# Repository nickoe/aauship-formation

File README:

AAUSHIP
=======

This repo is devoted develop and test formation control on AAUSHIP

http://auv.aau.dk

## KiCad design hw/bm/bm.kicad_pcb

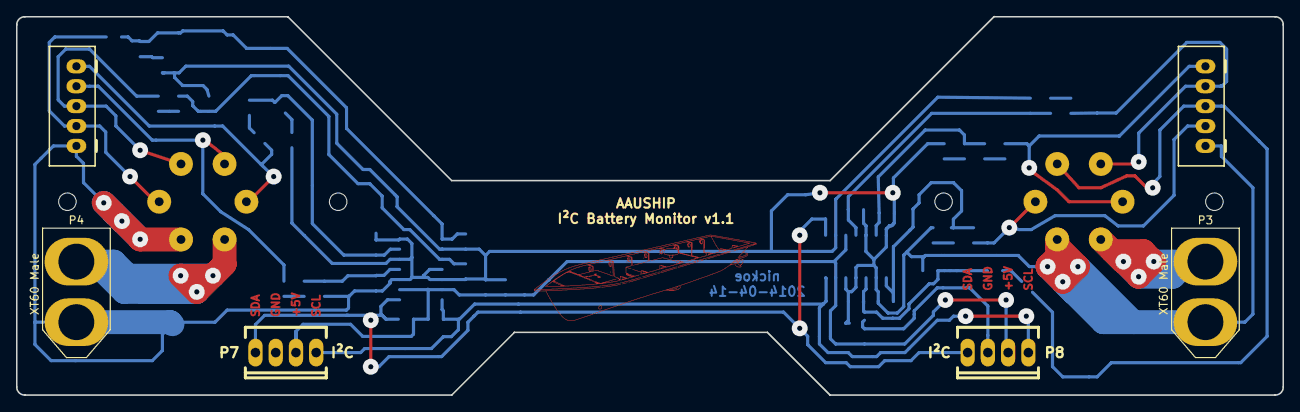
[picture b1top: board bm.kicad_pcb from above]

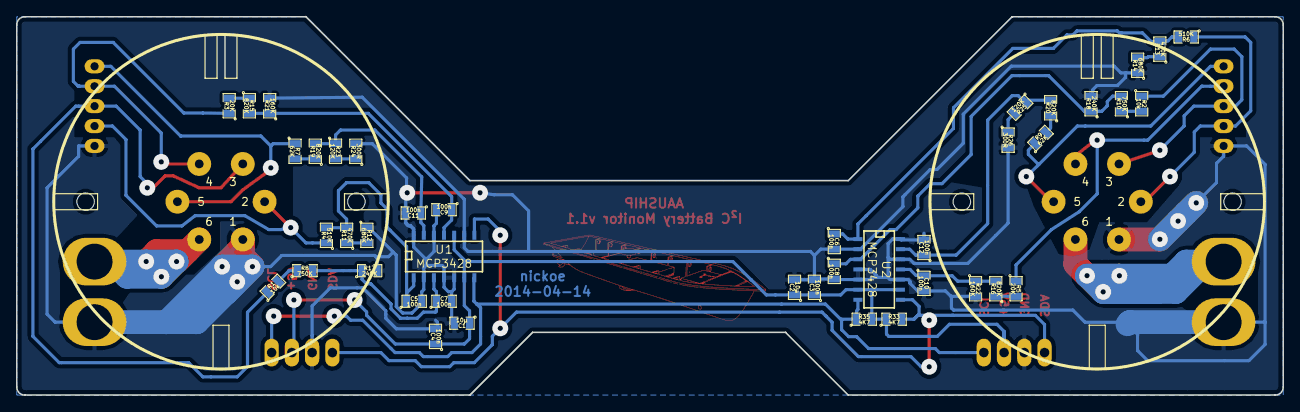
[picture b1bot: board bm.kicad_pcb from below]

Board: 2 copper layers, 159.0 x 47.5 mm, 51 parts (44 on the bottom side), 32 nets.

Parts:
C1, C2: 10µ; SM0805
C3, C4, C5, C6, C7, C8, C9, C10, C11, C12: 100n; SM0805
P1, P2: PX0707/06S; PX0707-S-6
P3, P4: XT60 Male; XT60
P5, P6: JST-XH; JST-B5B-XH-A
P7, P8: I²C; Socket_MOLEX-KK-RM2-54mm_Lock_4pin_straight
R1, R2: 10k; SM0805
R3, R5: 20K; SM0805
R4, R6: 510K; SM0805
R7, R9: 62K; SM0805
R8, R10: 750K; SM0805
R11, R13: 470K; SM0805
R12, R14: 680K; SM0805
R15, R16, R19, R20: 820K; SM0805
R17, R18: 240K; SM0805
R21, R22: 160K; SM0805
R23, R25: 120K; SM0805
R24, R26: 300R; SM0805
R33, R35: 4K7; SM0805
U1, U2: MCP3428; SO14E
VAL: aauship

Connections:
+5V: C1.1, C2.1, C3.1, C4.1, P7.2, P8.2, R33.1, R35.2, U1.6, U1.10, U2.6, U2.9
GND: C1.2, C2.2, C3.2, C4.2, C5.2, C6.2, C7.2, C8.2, C9.2, C10.2, C11.2, C12.2, P1.1, P2.1, P3.1, P4.1, P5.1, P6.1, P7.3, P8.3, R12.1, R14.1, R17.2, R18.2, R21.2, R22.2, R24.2, R26.2, U1.2, U1.4, U1.5, U1.9, U1.12, U1.14, U2.2, U2.4, U2.5, U2.10, U2.12, U2.14
unnamed: C5.1, R4.2, R11.2, U1.1
unnamed: C6.1, R6.2, R13.2, U2.1
unnamed: C7.1, R8.2, R17.1, U1.3
unnamed: C8.1, R10.2, R18.1, U2.3
unnamed: C9.1, R15.2, R21.1, U1.11
unnamed: C10.1, R16.2, R22.1, U2.11
unnamed: C11.1, R19.2, R23.1, U1.13
unnamed: C12.1, R20.2, R25.1, U2.13
unnamed: P1.2, P5.2, R4.1
unnamed: P1.3, P5.3, R1.1
unnamed: P1.4, P5.4, R3.1
unnamed: P1.5, P5.5, R7.1
unnamed: P1.6, P3.2
unnamed: P2.2, P6.2, R6.1
unnamed: P2.3, P6.3, R2.1
unnamed: P2.4, P6.4, R5.1
unnamed: P2.5, P6.5, R9.1
unnamed: P2.6, P4.2
unnamed: P7.1, P8.1, R35.1, U1.7, U2.7
unnamed: P7.4, P8.4, R33.2, U1.8, U2.8
unnamed: R1.2, R8.1
unnamed: R2.2, R10.1
unnamed: R11.1, R12.2
unnamed: R13.1, R14.2
unnamed: R3.2, R15.1
unnamed: R5.2, R16.1
unnamed: R7.2, R19.1
unnamed: R9.2, R20.1
unnamed: R23.2, R24.1
unnamed: R25.2, R26.1

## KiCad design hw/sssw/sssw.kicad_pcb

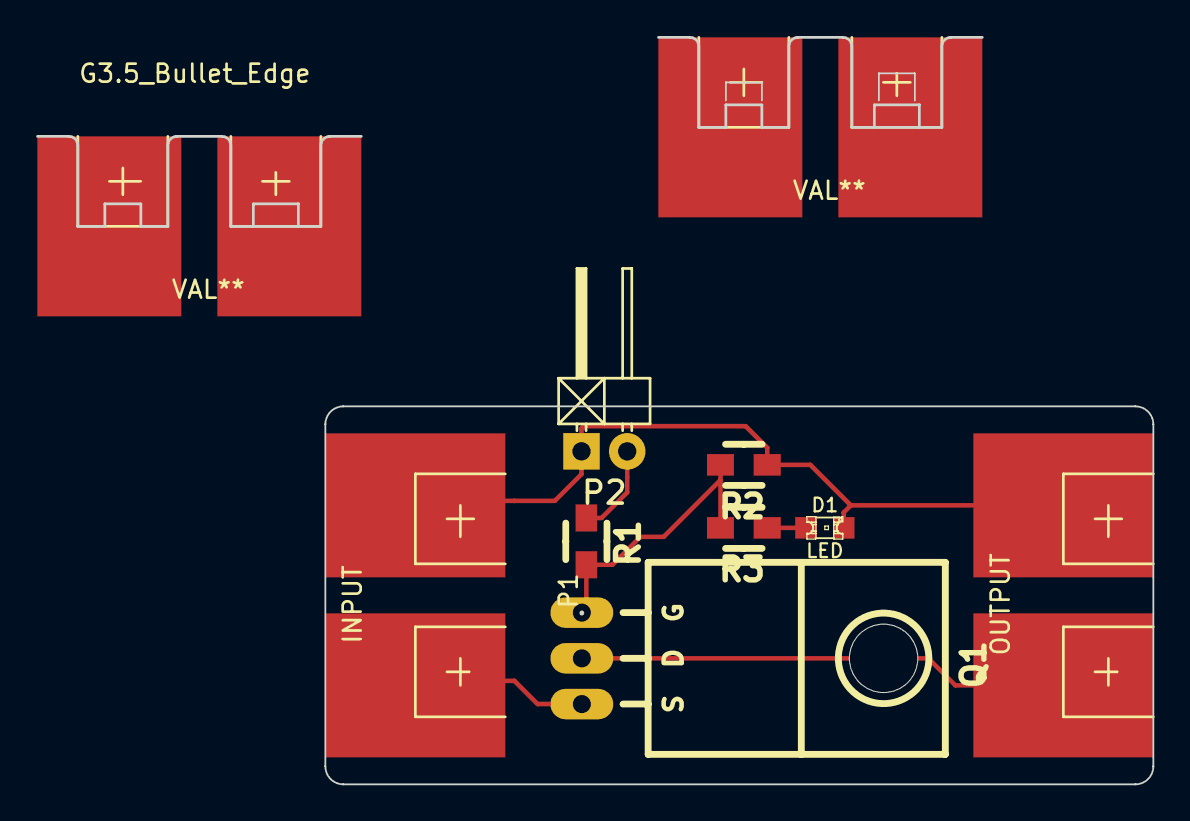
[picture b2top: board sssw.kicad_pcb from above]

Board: 2 copper layers, 61.9 x 41.4 mm, 10 parts (0 on the bottom side), 6 nets.

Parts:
D1: LED; LED-0805
G3.5_Bullet_Edge, G3.5_Bullet_Edge#2: VAL**; G3.5_Bullet_Edge
P1: INPUT; G3.5_Bullet_Edge
P2: ACTIVATE; Pin_Header_Angled_1x02
P3: OUTPUT; G3.5_Bullet_Edge
Q1: SUP85; TO-220_FET-GDS_Horizontal_LargePads
R1: 10K; Resistor_SMD0805_HandSoldering
R2: 1K; Resistor_SMD0805_HandSoldering
R3: 330; Resistor_SMD0805_HandSoldering

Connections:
GND: D1.2, P1.1, P2.1, P3.1, R2.1
unnamed: D1.1, R3.1
unnamed: P1.2, Q1.S
unnamed: P2.2, R1.1
unnamed: P3.2, Q1.D
unnamed: Q1.G, R1.2, R2.2, R3.2

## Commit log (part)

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2014-09-19 Fix sign
2014-09-19 Silence some output
2014-09-22 Try to publish tf in the control node instead of the kf node
2014-09-29 Worksheet9
2014-09-29 Add strategy bullets
2014-09-30 skrevet lidt til, skriver nok emre efter snak senere
2014-09-30 sat de sidste opapers ind i oversigt
2014-09-30 Grey out papers
2014-10-01 Add citations
2014-10-01 skrevet en strat mere ind - Nu skal vi undersøge dem nærmere
2014-10-02 lavet doc tilat skrive om null space beased behavioural
2014-10-08 har skrevet lidt til potentialfield, men det er svaert
2014-10-09 skrevet og addet lidt til bib
2014-10-13 Minor notes on potential fields
2014-10-13 Remove stupid file
2014-10-13 skrevet sammen og omstruktureret i potential field
2014-10-13 ups, mergede forkert. Fixet dette.
2014-10-14 underlige fejl med citat
2014-10-14 lavet bib og skrevet lidt til leader follower
2014-10-15 skrevet til leader follower og lavet oversigt med punkter
2014-10-15 skrevet til nogle, men meget hurtigt vil jeg mene
2014-10-15 skrevet one minima potential
2014-10-15 Not much to change actually
2014-10-17 Add link to workshop paper
2014-10-19 Minor changes to sssw
2014-10-20 skrevet ind i tabel, ikke uddybet, men det kan goeres naar den maaske kan blive hoejere
2014-10-21 skrevet om de 5 main criteria
2014-10-21 mere mere
2014-10-21 IP, IPv4, IPv6
2014-10-22 Remove old table
2014-10-23 Fixes #1
2014-10-23 Remove publishing of map in the simulaiton node, it is now available in the kalman filter node
2014-10-23 Add convent launch file
2014-10-23 Remove campus stuff, was a bad idea.
2014-10-23 skrevet til og rettet tabel
2014-10-23 Fix compile errors
2014-10-24 fix nmea gps log with new log file now plot is ok
2014-10-25 Fix D, G and MRB according to openloopplots.m
2014-10-26 kontrolleret og rettet i identification fil
2014-10-27 rettet fortegnsfejl, som jeg havde glemt
2014-10-27 så har vi lavet en tabel, hurra
2014-10-28 woop woop
2014-10-28 Beamer
2014-10-30 Remove some slides
2014-10-30 sat bilelde ind
2014-10-31 rettet til, tjekket op og lavet todo i rapport
2014-11-03 rigtig thrust alloc og forsoeg med KF, jeppepub
2014-11-03 skrevet om metoden fra UAV paperet
2014-11-03 Update to worksheet 11
2014-11-07 Remove unnessesarey print
2014-11-07 Fix thruster assignment and use the estimate from the kf node
2014-11-08 Add offeset to map
2014-11-10 Add addpath for AHRS algorithims
2014-11-10 Make the sensor playback in python instead of matlab
    Because the ROS IO matlab does not make it easy to use custom topics
2014-11-10 skrevet lidt til, men naaede ikke saa langt
2014-11-10 Fix some numbers in the gps publishing for the sensor-playback. Not heavily tested, but seems wto work ok.
2014-11-11 Fix unitialized variables
2014-11-11 Add double-simulation-aauship.launch
2014-11-11 Fix merge conflict
2014-11-11 Add ros bag support to the simulation launch file
2014-11-11 Save more info\!
2014-11-11 Step launch file
2014-11-12 Single ducking follower working, crude implemtation, not easily expandable
2014-11-17 Update udev rules with alias for mb100 devices
    mb100rover is 115200 baud
2014-11-18 Add indexes
2014-11-18 MB100 node that should work, not tested on hardware
2014-11-19 MB100 node ready to be tested
2014-11-19 er ved at lave ting og sager til pot field
2014-11-19 Add launch for mb100
2014-11-19 Add RomBOOT check
2014-11-20 hmm, forstaar ikke hvorfor fij ikke ligger i -2,-2..
2014-11-20 plots i fuld gang, men stadig tvivl omkring Fij placering
2014-11-20 use /dev/mb100rover
2014-11-20 Fix for the mb100 kftrack topic not being plottet.
    It was plotting the same point for both ends of the ine segment
2014-11-21 Add parser for the $PASHR,POS messages
2014-11-23 tests m plots m fejl
2014-11-24 Enable echosounder logging
2014-11-24 lavet thrust input og lavet flere paths vi kan følge
2014-11-24 Add some formatting for the process.m
2014-11-24 Control node as is
2014-11-24 lavet flere paths
2014-11-24 add *.mat to gitignore
2014-11-24 lavet plot indikation på fig8
2014-11-24 Add templates for the tracks
2014-11-24 Update rviz config
2014-11-24 lavet større linje segment af to wps
2014-11-24 tests osv rundt i en masse filer
2014-11-25 Fik ikke lige imp min max, men der er MOAR PLOTS
2014-11-26 Add input log
2014-11-26 ja ja
2014-11-26 rigtige plots, dog stadig uden path lige nu
2014-11-27 pew pew moar plots
2014-11-27 mere end en anden båd
2014-11-30 moar plots in function now
2014-11-30 Fix use of wrong variable
2014-12-01 Make compatible with parfor
2014-12-01 flyttet rundt og forstørret
2014-12-01 lavet pathgen som funktion
2014-12-01 skrevet omkring pot field, lidt løst og lidt fast
2014-12-01 Fix minor errors
2014-12-02 moar plots, men dog ikke helt rigtige ej heller overskuelige :S
2014-12-03 har ikke addet trajectory endnu
2014-12-05 Draft for oceans15 abstract
2014-12-05 addet jespers tilføjelser i anden fil
2014-12-05 skrevet jespers ind i fil
2014-12-05 mangelede noget tekst
2014-12-07 Add potentialfield block diagram
2014-12-08 nu virker quiver plots igen, de skal bruge original meshgrids
2014-12-09 nu virker quiver og alle de andre plots igen igen. Byttet om på index af n og m i tæller.
2014-12-09 nu kan nick pull
2014-12-09 Update pot field block svg
2014-12-10 wk12 template
2014-12-10 klargør en merge
2014-12-11 skrevet lidt til, forklaring af kræfter
2014-12-11 Add mising ref
2014-12-11 rettet i noget
2014-12-13 Add non working simaauship2.m
2014-12-13 potential field simulation, without ship dynamics and proper fvl convergence, working.
2014-12-15 With the model, they sail the wrong way
2014-12-15 Add seperate control chapter
2014-12-15 Rearrange doc
2014-12-15 Polygoooonnnn!
2014-12-15 skriver til tabel, efter det skriver jeg omkring strategierne, 2 og 3
2014-12-16 Update ton wk 13
2014-12-16 skrevet til hist og her
2014-12-16 skrevet en ny ref
2014-12-16 Fix yypos
2014-12-16 Fix case
2014-12-17 lavet fig om, skrevet tekst dertil om. fig 4.1, hvis den ikke er flyttet i nummer.
2014-12-17 Fix some typography
2014-12-18 Correct some errors form the feedback on the potential field chapter
2014-12-18 Fix eq
2014-12-18 skrevet lidt til en loesning paa roevproblem
2014-12-19 skrevet caption til fig om
2014-12-21 skrevet i control.tex og rettet til i billede til at cluster agents/objects
2014-12-21 gramatics
2014-12-21 rettet lidt til og inddelt i afsnit. Nu rettes ting til vektorer med bf.
2014-12-21 nu er alle p og d som skal være bf lavet til bf
2014-12-21 vil skrive under algebra afsnittet
2014-12-22 skriver under algebra afsnit, skal til at dokumentere sign fcn
2014-12-23 Fix model
2014-12-25 Add fjorden.mat
2014-12-25 har skrevet meget lidt mere
2014-12-25 lavet wps til seatrials
2014-12-25 Fix fix num
2014-12-25 Add other track alternatives
2014-12-26 More surge force
2014-12-26 der er måske noget formation som virker
2014-12-28 Fix typo in bib
2014-12-28 Fix some typos and add some comments in some todos
2014-12-30 Fix paragraph seperation
2014-12-30 flyttet på afsnit og lavet endnu en todo, da jeg ikke kan se hvordan det afsnit med path gen skal flettes. For mig at se er det et helt andet afsnit, men måske er det fordi jeg ikke er klar over hvad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
2014-12-31 lavet en hurtig fig af form. startpunkt skal nok ændres.
2014-12-31 skrevet lidt til potform figuren, men denne skal laves ordentlig snarest, hvor teksten også skal udfyldes lidt mere
2014-12-31 lavede lige en update til en todo
2015-01-02 Fix version numbers on BM
2015-01-02 Add LTspice simulations
2015-01-02 rettet alle sign-f til sign f og skrevet pot field inden pot field strat om så det giver mere mening
2015-01-02 okay, glemte et par stykker af de der sign-f
2015-01-02 Fix typo
2015-01-02 skrevet ved en todo
2015-01-02 Add missing png
2015-01-02 Add ADC
2015-01-03 Fix pcb image
2015-01-03 Finish bm appendix
2015-01-03 skrevet lidt hist og her, og har lavet noter til at skrive thrustalloc korrekt
2015-01-03 rettet bm.tex til, den er fin nu
2015-01-03 rettet hist og her
2015-01-03 Adjust bm.tex
2015-01-03 simaauship2.m for the lawnmover formation bar plot
2015-01-03 fjordtur
2015-01-03 skrevet til thrust alloc. det skal læses igennem inden aflevering.
2015-01-03 glemte lige rækkefølge på XYZKMN
2015-01-04 lavede lige et billede og skrev til det i thrustalloc
2015-01-04 ændrede noget tilbage
2015-01-04 lavet en ref og skrevet lidt kort. Skriver videre om lidt.
2015-01-04 skrevet i pathgen
2015-01-04 udkommenteret at der skal vedhæftes et paper
2015-01-05 rettet til, og ændret til 15x15 system matrix og hvad det medfører
2015-01-05 skrevet matricer ind med tal fra appendix op i afsluttende i rapport under identification of hydrodynamic derivatives
2015-01-06 ved at skrive ting og sager
2015-01-06 skrevet eta dot ind
2015-01-06 Fix missing variable on fig
2015-01-06 Something in fig changed
2015-01-06 skrevet lidt om Alba i intro
2015-01-06 Fix some stuff in manual
2015-01-06 Fix alba
2015-01-06 en masse ting tror jeg
2015-01-06 skrevet ang Klingen turen og indkluderet en stor pdf :D
2015-01-06 skrevet en todo mere
2015-01-07 a sandbar and not a beach bar
2015-01-07 rettet fig
2015-01-07 Add observation state variables on figure
2015-01-07 lavet den nye figur og skrevet mere beskrivende til den
2015-01-07 lavet en surge verify
2015-01-07 Split paragraphs into more, for better readability.
2015-01-07 lavet en fig mere og skrevet lidt hist og her
2015-01-07 lavet og rettet i plots
2015-01-07 skrevet lidt om pitch angle under surgevel
2015-01-07 move ahrs doc
2015-01-07 skrevet udkast til preface og synopsis
2015-01-07 og lavet dokumentet til at skrive det i
2015-01-07 Fix some todos
2015-01-07 Minor changes in front matter
2015-01-07 skrevet noget til conclusion og tilføjet labels igen i rapporten
2015-01-08 rettet og lavet todo til update af antal appendix
2015-01-08 rettet preface og lavet en todo med ref til github
2015-01-08 rette chapter II
2015-01-08 chapter III rettet
2015-01-08 Add some stuff
2015-01-08 rettet chapter V
2015-01-08 rettet simulation_model.tex
2015-01-08 Add plots
2015-01-08 rettet chapter 7
2015-01-08 rettet ros chapter
2015-01-08 appendix
2015-01-08 bollardpull rettet
2015-01-08 Fix some formatting in appendix aboyt the hydro derivatives
2015-01-08 app var rettet
2015-01-08 Minor fixes
2015-01-08 Fix fig
2015-01-08 retett todo fejl i title page
2015-01-08 update frontpage
2015-01-08 jeg skal skide
2015-01-08 Other title type
2015-01-08 rettet appendix antal, udkommenteret todo
2015-01-08 rettet schapter
2015-01-08 rettet wifi til wi-fi
2015-01-08 Try to fix link
2015-01-08 Add missing pngs
2015-01-08 fix preface
2015-01-08 more fixing
2015-01-08 Add danish titlepage template
2015-01-08 det er abre woojd
2015-01-20 min version af simaauship2 indtil nu
2015-01-21 check virker ordentligt nu
2015-01-21 Fix some plots
2015-01-21 Simple animation of the formation from simaauship2.m
2015-01-22 Some minor improvements
2015-01-22 Now with constant speed feature... not ideal yet
2015-01-22 Circle madness for jeppe
2015-01-23 Fix some formation with a sort of constant speed
    There are currently still jumps when reaching a waypoint, this needs
    to be solved
2015-01-23 Fix some issues
    Still needs to handle speed in inital fomation waiting configuration
2015-01-23 We should try to fix the loop issue for the blue boat here
2015-01-26 Fix track loop issue
2015-01-27 Fix rad2pipi on plot
2015-01-27 Fix plot again
2015-01-27 illu af non feasable track
2015-01-27 Fix formation, wee...
2015-01-28 script til at generere plots fra
2015-01-28 lavet plots som skal med og sat dem ind i tex
2015-01-29 Fix RTK block diagram
2015-01-29 update beamer
2015-01-29 bom bom bom
2015-01-29 mere til præsentation
2015-01-29 hej hej
2015-01-29 fix size
2015-01-29 klar til merge
2015-01-29 indsaet svg fig til pot field
2015-01-29 så er tex filen der også
2015-01-29 itemize
2015-01-29 remove slide
